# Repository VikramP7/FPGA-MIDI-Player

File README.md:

*<div align="right"> Vikram Procter | Nov, 2025 </div>*

# FPGA MIDI Buzzer Player

## Project Overview
  
*Photo of finished project*

Using a Basys3 Artix-7 FPGA development board I designed an  SystemVerilog framework to playback MIDI music to a buzzer. The project uses python scripts I wrote to parse MIDI files and generate ready to use SystemVerilog files that store the music data. 

This project was an extension for a final project for ENEL 453 a Digital Systems Design course at University of Calgary. The original project required us to create an ADC circuit and the required digital architecture to operate and display the ADC value. 

## Systems Overview
  
*RTL Schematic Generated Using Vivado*

The buzzer music playback system is built from three main functional modules: *Song Player Timer, Buzzer PWM, Volume Control*. These modules are supported by 3 look up table memory segments, MIDI Index to PWM Period, the song note pitches and the song note durations. The song’s note pitches and durations are stored serially in memory and dictates the PWM frequency supplied to the buzzer and how long each frequency is played for. The buzzer volume can also be adjusted using the analog input to the ADCs implemented in the original project.

A custom PCB was designed to connect to the headers of the Basys3 board, this allowed for easy connection to the pins of the R2R ladder used as a DAC, to create a variable analog voltage, and connect to the buzzer. This board was developed in KiCad and the files can be found in the repo.

The ADC portion of the ENEL 453 project was completed as a group project with Caleb Garcia and Chloe Fulbrook. You can find the full repo to all of the project files here: [https://github.com/cwlebgarcia/ENEL-453](https://github.com/cwlebgarcia/ENEL-453)

## MIDI Music Player 
### Python MIDI interpreter

The `MidiToBoard.py` uses the Mido python library which extracts each of the midi files messages into a python friendly list. My program parses through each of these messages identifying each note pitch and duration. The provided MIDI duration is in ticks and a calculation using the provided tempo messages is done to convert the tick count durations into micro-seconds. This program produces two lists, one containing the pitches for each note in the song and the other holds the duration of each note (in us).

The `gen.py` script uses the lists generated by `MidiToBoard.py` to creates two SystemVerilog files for the note pitches and the note durations. These pairs of files make up each song and are added to the project, where select switches and a mux determine which song is played.

```systemverilog
module song0_dur #(
    parameter int CLOCK_FREQ = 100_000_000
) (
    input logic [10:0] note_index,
    output logic [28:0] note_dur // max 10s at 100MHz clock
);

localparam real TEMPO_BPM = 120;
localparam real CYCLES_PER_BEAT = CLOCK_FREQ*(60/TEMPO_BPM);

always_comb begin
    // the quarter note is one beat and therefore can be multiplied by CYCLES_PER_BEAT
    case (note_index)
        0: note_dur = CYCLES_PER_BEAT * 0.65;
        1: note_dur = CYCLES_PER_BEAT * 0.1;
        2: note_dur = CYCLES_PER_BEAT * 0.25;
        ...
```

### SystemVerilog Music Playback Architecture
The Song Player Timer module drives the music playback. It increments through each note of the song as an index, keeping track of when each notes' duration has elapsed. The module references the *Note Duration Memory* to provide the length of the current note (`cur_note_dur`). When a different song is selected the module resets the note index and clears the elapsed time counter to start on the next track.

The Buzzer PWM module works in conjunction with a look up table that maps each MIDI note index (an index for all playable notes 0-127) to the  period of the PWM output needed to generate the note's frequency. The Buzzer PWM module outputs a 50%-duty-cycle PWM signal supplied to the buzzer.

*Buzzer Oscilloscope Trace Demonstrating Volume PWM*

The **Buzzer Volume Module** adjusts the buzzer's loudness using the averaged output of the selected ADC. This takes advantage of the low pass mechanical properties of the buzzer. The buzzer can’t physically respond to frequencies higher than ~15-20kHz. By driving the buzzer with a higher frequency, variable duty cycle PWM essentially a lower voltage can be provided to the buzzer. The output of the audio PWM is multiplied by this higher frequency voltage modulating PWM to achieve dynamic volume control. 

## The PCB 
The custom PCB integrates a PWM-low-pass-filter DAC unit along with a R2R ladder DAC used with a comparator to operate the ADCs. The PCB also uses a potentiometer to produce a variable analog voltage for testing the ADCs. As well, most importantly to this project the PCB also connects to the piezo-electric buzzer.

*PCB Schematic in KiCad*

*PCB Layout Schematic in KiCad*

*PCB Printed and Soldered*

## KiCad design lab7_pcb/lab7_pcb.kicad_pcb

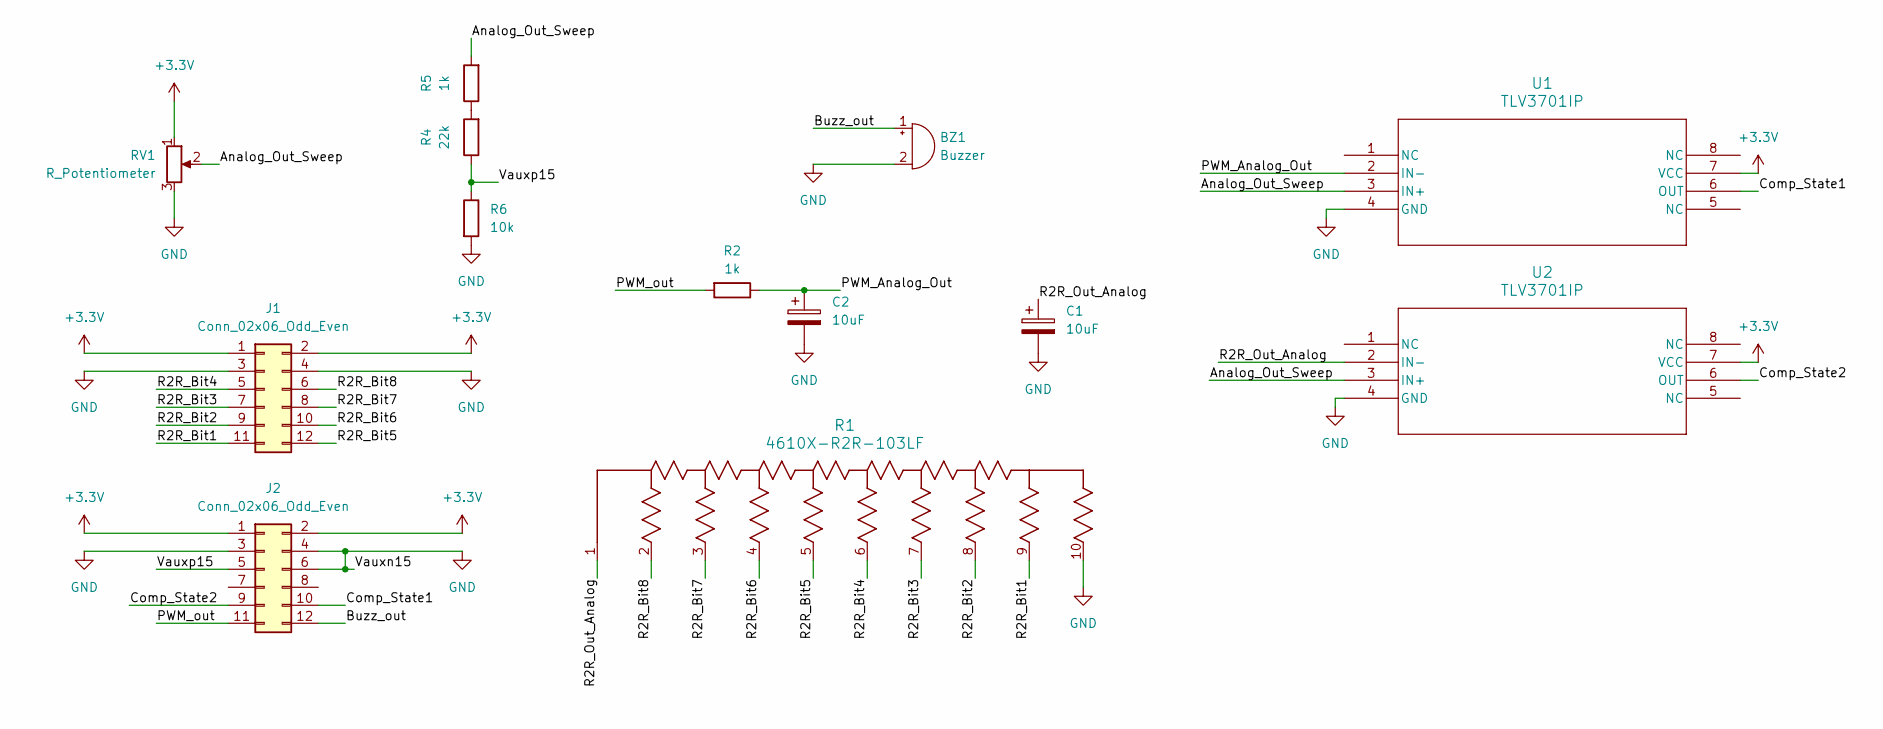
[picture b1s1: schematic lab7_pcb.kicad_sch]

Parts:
BZ1: Buzzer; Buzzer_12x9.5RM7.6
C1, C2: 10uF; CP_Radial_D5.0mm_P2.50mm
J1, J2: Conn_02x06_Odd_Even; PinHeader_2x06_P2.54mm_Horizontal
R1: 4610X-R2R-103LF; BO_4610X
R2, R5: 1k; R_Axial_DIN0309_L9.0mm_D3.2mm_P12.70mm_Horizontal
R4: 22k; R_Axial_DIN0309_L9.0mm_D3.2mm_P12.70mm_Horizontal
R6: 10k; R_Axial_DIN0309_L9.0mm_D3.2mm_P12.70mm_Horizontal
RV1: R_Potentiometer; Potentiometer_Vishay_148-149_Single_Vertical
U1, U2: TLV3701IP; P8

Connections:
+3.3V: J1.1, J1.2, J2.1, J2.2, RV1.1, U1.7 (VCC), U2.7 (VCC)
/Analog_Out_Sweep: R5.2, RV1.2, U1.3 (IN+), U2.3 (IN+)
/Buzz_out: BZ1.1 (+), J2.12
/Comp_State1: J2.10, U1.6 (OUT)
/Comp_State2: J2.9, U2.6 (OUT)
/PWM_Analog_Out: C2.1, R2.1, U1.2 (IN-)
/PWM_out: J2.11, R2.2
/R2R_Bit1: J1.11, R1.9
/R2R_Bit2: J1.9, R1.8
/R2R_Bit3: J1.7, R1.7
/R2R_Bit4: J1.5, R1.6
/R2R_Bit5: J1.12, R1.5
/R2R_Bit6: J1.10, R1.4
/R2R_Bit7: J1.8, R1.3
/R2R_Bit8: J1.6, R1.2
/R2R_Out_Analog: C1.1, R1.1, U2.2 (IN-)
/Vauxp15: J2.5, R4.1, R6.1
GND: BZ1.2 (-), C1.2, C2.2, J1.3, J1.4, J2.3, J2.4, J2.6, R1.10, R6.2, RV1.3, U1.4 (GND), U2.4 (GND)
unnamed: R4.2, R5.1

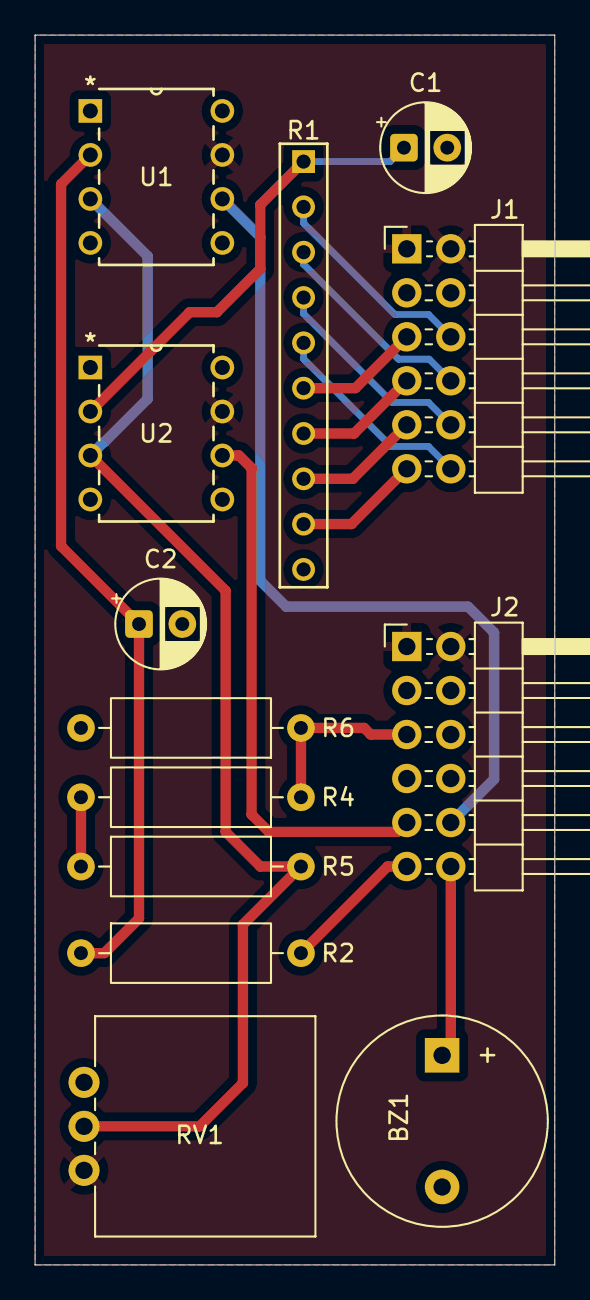
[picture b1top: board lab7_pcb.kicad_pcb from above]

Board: 2 copper layers, 30.0 x 71.0 mm, 13 parts (0 on the bottom side), 19 nets.

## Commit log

2025-12-01 Clean Up
2025-12-01 Added gitignore
2025-12-01 Renamed top level
2025-12-01 Renamed Folders and synthed design
2025-12-01 Added Readme
2025-12-01 Added Readme and project pictures
2025-12-01 umm i guess a synth file from vivado
2025-12-02 Finished Readme
